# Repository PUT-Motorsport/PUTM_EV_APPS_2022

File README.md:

# Accelerator Pedal Position Sensor (APPS)

## Motivation

APPS handling is required by official FSG Rules according to T11.8 ([see](https://www.formulastudent.de/fileadmin/user_upload/all/2022/rules/FS-Rules_2022_v1.0.pdf#page=58)). APPS signals are system critical signals meaning that any implausibility between sensors or a failure should result in complete motor power shutdown.

## Pedal travel

* 0% - fully released
* 100% - fully applied

## Implausiblity

Implausibility is defined as a deviation of more than ten percentage points pedal travel
between any of the used APPSs. If it occurs for more than 100 ms the power to the motor must be immediately shut down.

## Platform

Software for APPS signal handling is developed using C++ for STM32 microcontroller.

## Program schematic

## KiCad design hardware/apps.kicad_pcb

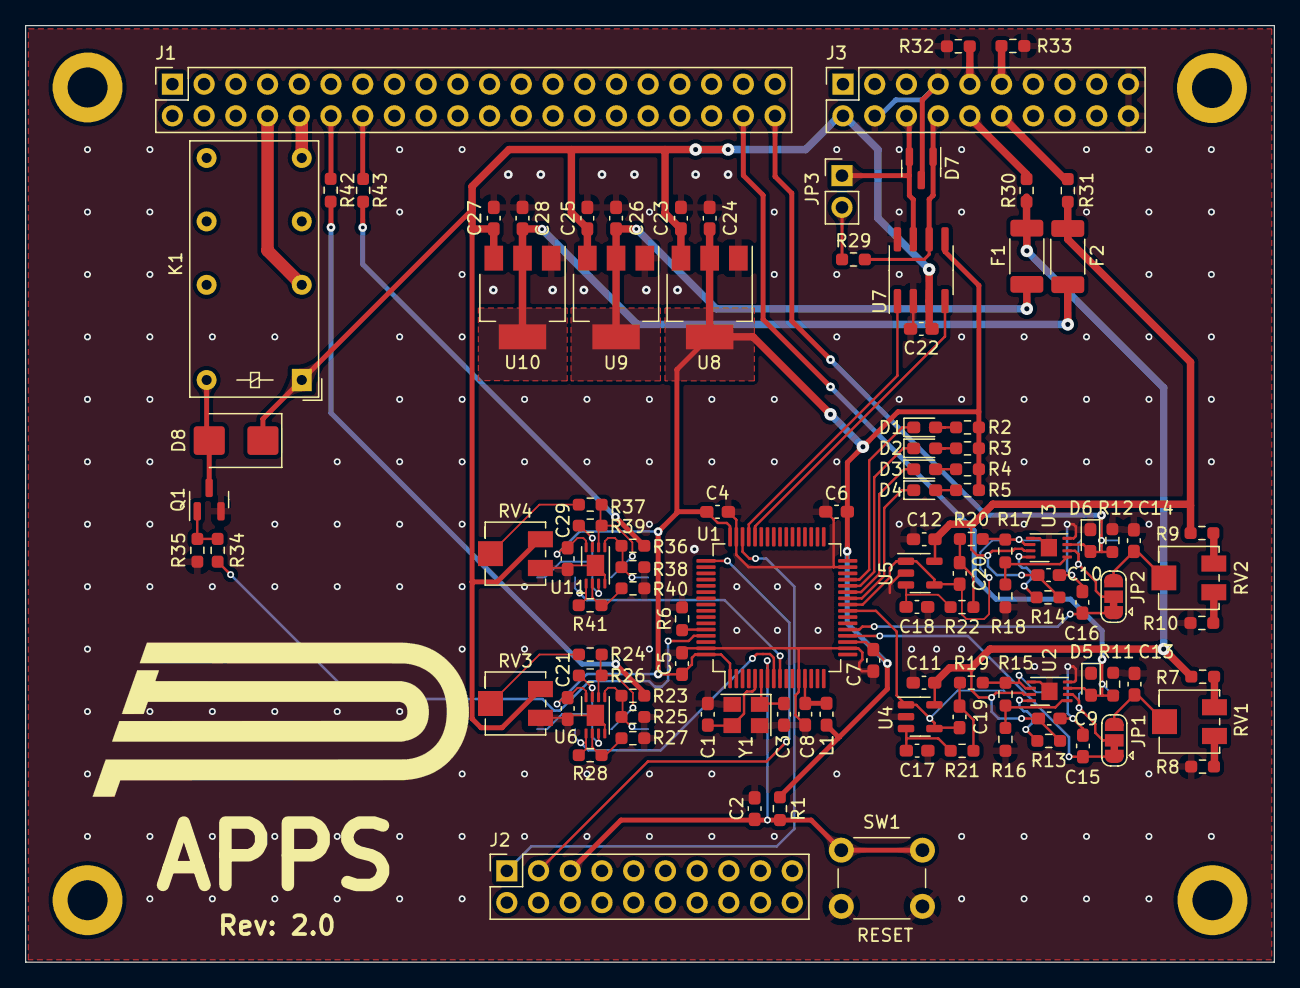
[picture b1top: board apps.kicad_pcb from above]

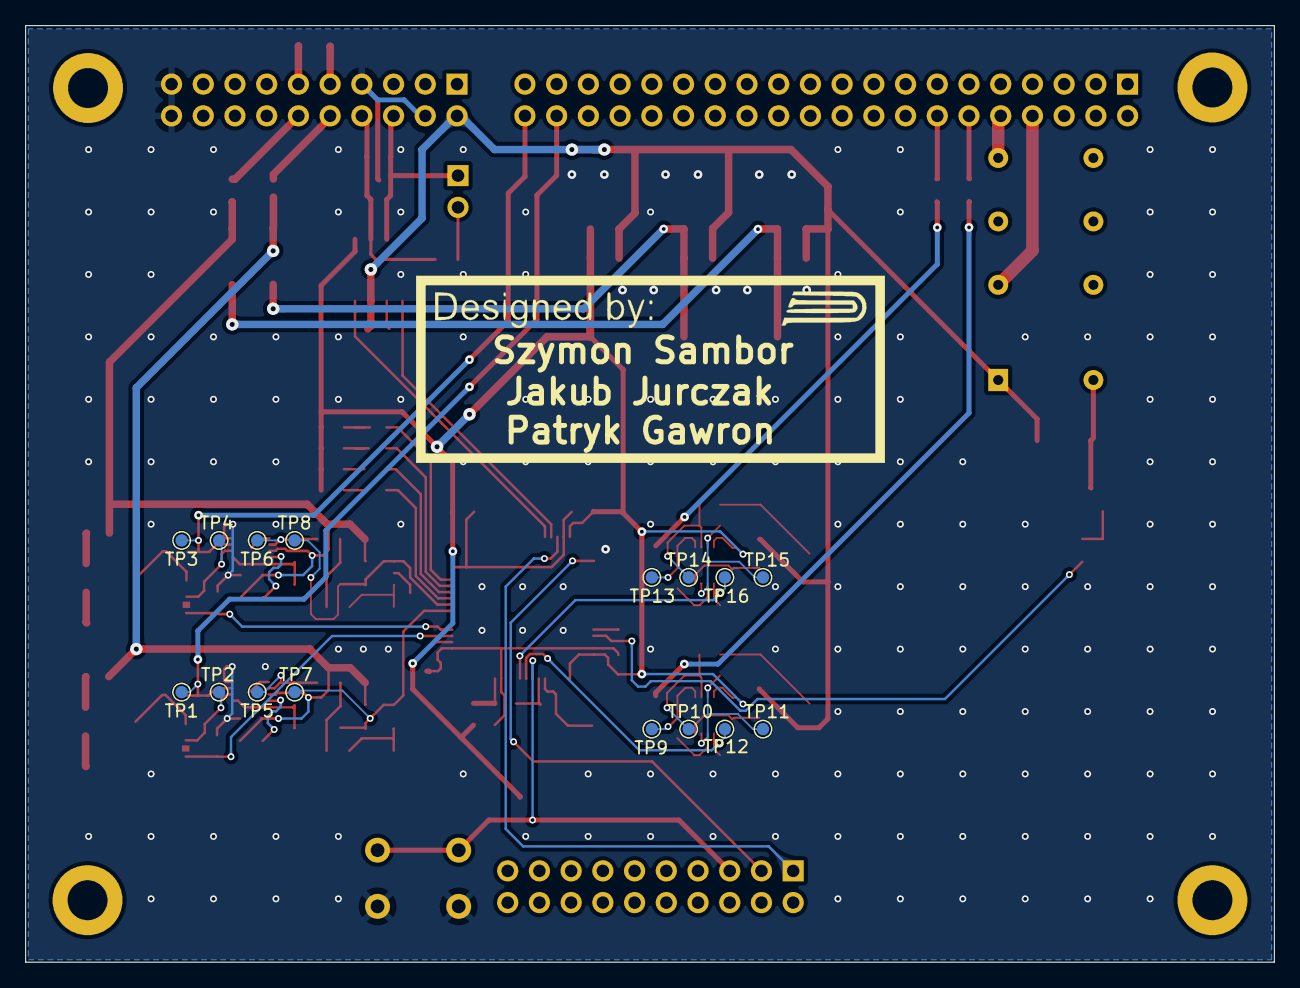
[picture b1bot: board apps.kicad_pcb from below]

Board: 2 copper layers, 100.0 x 75.0 mm, 124 parts (16 on the bottom side), 76 nets.

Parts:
C1, C3: 22p; C_0603_1608Metric_Pad1.08x0.95mm_HandSolder
C2, C4, C5, C6, C7, C8, C9, C10, C11, C12, C17, C18, C19, C20, C21, C22, C23, C24, C25, C26, C27, C28, C29: 100n; C_0603_1608Metric_Pad1.08x0.95mm_HandSolder
C13, C14, C15, C16: 10n; C_0603_1608Metric_Pad1.08x0.95mm_HandSolder
D1, D2, D3, D4: Yellow; LED_0603_1608Metric_Pad1.05x0.95mm_HandSolder
D5, D6: 24V; D_0603_1608Metric_Pad1.05x0.95mm_HandSolder
D7: PESD2CAN.215; SOT-23
D8: STPS340U; D_SMB
F1, F2: 500mA; Fuse_2010_5025Metric
J1: Signals; PinSocket_2x20_P2.54mm_Vertical
J2: Diagnostics; PinSocket_2x10_P2.54mm_Vertical
J3: Power & CAN; PinSocket_2x10_P2.54mm_Vertical
JP1, JP2: POT/DAC; SolderJumper-3_P1.3mm_Bridged12_RoundedPad1.0x1.5mm
JP3: Terminator; PinHeader_1x02_P2.54mm_Vertical
K1: FINDER-30.22; Relay_DPDT_Finder_30.22
L1: 10u; L_0603_1608Metric_Pad1.05x0.95mm_HandSolder
Q1: BSN20; SOT-23
R1, R6, R7, R9, R35: 10k; R_0603_1608Metric_Pad0.98x0.95mm_HandSolder
R2, R3, R4, R5: 300R; R_0603_1608Metric_Pad0.98x0.95mm_HandSolder
R8, R10: 33k; R_0603_1608Metric_Pad0.98x0.95mm_HandSolder
R11, R12: 100k; R_0603_1608Metric_Pad0.98x0.95mm_HandSolder
R13, R14, R23, R26, R28, R32, R36, R39, R41, R42, R43: 0R; R_0603_1608Metric_Pad0.98x0.95mm_HandSolder
R15, R19, R20, R21, R22: 4k7; R_0603_1608Metric_Pad0.98x0.95mm_HandSolder
R16, R18: 1k; R_0603_1608Metric_Pad0.98x0.95mm_HandSolder
R17: 6k2; R_0603_1608Metric_Pad0.98x0.95mm_HandSolder
R24, R25, R34, R37, R38: 100R; R_0603_1608Metric_Pad0.98x0.95mm_HandSolder
R27, R40: 3k3; R_0603_1608Metric_Pad0.98x0.95mm_HandSolder
R29: 120R; R_0603_1608Metric_Pad0.98x0.95mm_HandSolder
R30: 330R; R_0603_1608Metric_Pad0.98x0.95mm_HandSolder
R31, R33: 220R; R_0603_1608Metric_Pad0.98x0.95mm_HandSolder
RV1, RV2: 1k; Potentiometer_Bourns_3214J_Horizontal
RV3, RV4: 2k; Potentiometer_Bourns_3214J_Horizontal
SW1: Reset; SW_PUSH_6mm
TP1, TP3: APPS_P; TestPoint_Pad_D1.0mm
TP2, TP4: APPS_N; TestPoint_Pad_D1.0mm
TP5, TP6: APPS_MID; TestPoint_Pad_D1.0mm
TP7, TP8: APPS_OUT; TestPoint_Pad_D1.0mm
TP9, TP13: BR_P; TestPoint_Pad_D1.0mm
TP10, TP14: BR_N; TestPoint_Pad_D1.0mm
TP11, TP15: BR_MID; TestPoint_Pad_D1.0mm
TP12, TP16: BR_OUT; TestPoint_Pad_D1.0mm
U1: STM32L4P5RET6; LQFP-64_10x10mm_P0.5mm
U2, U3: MCP6N11-005; TDFN-8-1EP_3x2mm_P0.5mm_EP1.3x1.4mm
U4, U5: MCP6001; SOT-23-5
U6, U11: MCP6002-xMC; DFN-8-1EP_3x2mm_P0.5mm_EP1.7x1.4mm
U7: MCP2562-H-SN; SOIC-8_3.9x4.9mm_P1.27mm
U8, U9, U10: LM1117-3.3; SOT-223-3_TabPin2
Y1: 8MHz; Crystal_SMD_3225-4Pin_3.2x2.5mm

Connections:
3V3_POT1: C9.1, C11.1, F1.1, R7.1, R13.2, R30.1, U2.7 (V+), U4.5 (V+)
3V3_POT2: C10.1, C12.1, F2.1, R9.1, R14.2, R31.1, U3.7 (V+), U5.5 (V+)
+3V3: C4.1, C5.1, C6.1, C7.1, C21.1, C24.1, C29.1, L1.1, R1.2, R2.1, R3.2, R4.2, R5.1, U1.1 (VBAT), U1.19 (VDD), U1.32 (VDD), U1.48 (VDDUSB), U1.64 (VDD), U6.8 (V+), U7.5 (Vio), U8.2 (VO), U11.8 (V+)
+5V: C22.1, C23.1, C25.1, C27.1, D8.1 (K), J3.2, K1.A1, RV3.1, RV4.1, U7.3 (VDD), U8.3 (VI), U9.3 (VI), U10.3 (VI)
/APPS1: C19.2, TP7.1, U1.24 (PC4), U4.1, U4.4 (-)
/APPS2: C20.2, TP8.1, U1.25 (PC5), U5.1, U5.4 (-)
/BRK_PRESS1: R28.1, TP12.1, U1.8 (PC0), U6.1
/BRK_PRESS2: R41.1, TP16.1, U1.9 (PC1), U11.1
/CAN_RX: U1.44 (PA11), U7.4 (RXD)
/CAN_TX: U1.45 (PA12), U7.1 (TXD)
/DAC_REF1: C15.1, JP1.1 (A), U1.20 (PA4)
/DAC_REF2: C16.1, JP2.1 (A), U1.21 (PA5)
/EN_RELAY: R34.2, U1.61 (PB8)
/LED1: D1.1 (K), U1.29 (PB10)
/LED2: D2.1 (K), U1.28 (PB2)
/LED3: D3.1 (K), U1.27 (PB1)
/LED4: D4.1 (K), U1.26 (PB0)
/XTAL1: C1.1, U1.5 (PH0-OSC_IN), Y1.3
/XTAL2: C3.1, U1.6 (PH1-OSC_OUT), Y1.1
BRK_PRESS_LEFT: R23.2, R42.1
BRK_PRESS_RIGHT: R36.2, R43.1
CAN+: D7.2 (A2), J3.6, JP3.1, U7.7 (CANH)
CAN-: D7.1 (A1), J3.8, R29.2, U7.6 (CANL)
CLK: J2.3, U1.49 (PA14)
GND: C1.2, C2.2, C3.2, C4.2, C5.2, C6.2, C7.2, C8.2, C9.2, C10.2, C11.2, C12.2, C13.2, C14.2, C15.2, C16.2, C17.2, C18.2, C21.2, C22.2, C23.2, C24.2, C25.2, C26.2, C27.2, C28.2, C29.2, D5.1 (A1), D6.1 (A1), D7.3 (common), J3.4, J3.7, J3.19, J3.20, Q1.2 (S), R6.1, R8.2, R10.2, R11.2, R12.2, R16.1, R18.1, R25.1, R27.2, R32.1, R33.1, R35.2, R38.1, R40.2, RV3.3, RV4.3, SW1.1, U1.12 (VSSA/VREF-), U1.18 (VSS), U1.31 (VSS), U1.47 (VSS), U1.63 (VSS), U2.4 (V-), U2.5 (RF), U2.9 (EP), U3.4 (V-), U3.5 (RF), U3.9 (EP), U4.2 (V-), U5.2 (V-), U6.4 (V-), U6.9 (V-), U7.2 (VSS), U7.8 (STBY), U8.1 (GND), U9.1 (GND), U10.1 (GND), U11.4 (V-), U11.9 (V-), Y1.2, Y1.4
NRST: C2.1, J2.5, R1.1, SW1.2, U1.7 (NRST)
unnamed: C19.1, R19.2, R21.1
unnamed: C20.1, R20.2, R22.1
unnamed: D1.2 (A), R2.2
unnamed: D2.2 (A), R3.1
unnamed: D3.2 (A), R4.1
unnamed: D4.2 (A), R5.2
unnamed: D8.2 (A), K1.A2, Q1.3 (D)
unnamed: J1.12, R42.2
unnamed: J1.14, R43.2
unnamed: J3.9, R32.2
unnamed: J3.10, R30.2
unnamed: J3.11, R33.2
unnamed: J3.12, R31.2
unnamed: C13.1, JP1.3 (B), RV1.2
unnamed: JP1.2 (C), TP2.1, U2.2 (-)
unnamed: C14.1, JP2.3 (B), RV2.2
unnamed: JP2.2 (C), TP4.1, U3.2 (-)
unnamed: JP3.2, R29.1
unnamed: Q1.1 (G), R34.1, R35.1
unnamed: R7.2, RV1.1
unnamed: R8.1, RV1.3
unnamed: R9.2, RV2.1
unnamed: R10.1, RV2.3
unnamed: R15.2, R19.1, TP5.1, U2.6
unnamed: R17.2, R20.1, TP6.1, U3.6
unnamed: R24.2, RV3.2
unnamed: R37.2, RV4.2
unnamed: R6.2, U1.60 (PH3-BOOT)
unnamed: R13.1, U2.8 (EN)
unnamed: R15.1, R16.2, U2.1 (FG)
unnamed: R14.1, U3.8 (EN)
unnamed: R17.1, R18.2, U3.1 (FG)
unnamed: C17.1, R21.2, U4.3 (+)
unnamed: C18.1, R22.2, U5.3 (+)
unnamed: R26.1, TP11.1, U6.3 (+), U6.7
unnamed: R27.1, R28.2, U6.2 (-)
unnamed: R23.1, R25.2, TP9.1, U6.5 (+)
unnamed: R24.1, R26.2, TP10.1, U6.6 (-)
unnamed: C26.1, F1.2, U9.2 (VO)
unnamed: C28.1, F2.2, U10.2 (VO)
unnamed: R39.1, TP15.1, U11.3 (+), U11.7
unnamed: R40.1, R41.2, U11.2 (-)
unnamed: R36.1, R38.2, TP13.1, U11.5 (+)
unnamed: R37.1, R39.2, TP14.1, U11.6 (-)
SAFETY_IN: J1.8, K1.11
SAFETY_OUT: J1.10, K1.14
SIG_APPS1: D5.2 (A2), J1.38, R11.1, TP1.1, U2.3 (+)
SIG_APPS2: D6.2 (A2), J1.40, R12.1, TP3.1, U3.3 (+)
SWD: J2.1, U1.46 (PA13)
VDDA: C8.1, L1.2, U1.13 (VDDA/VREF+)

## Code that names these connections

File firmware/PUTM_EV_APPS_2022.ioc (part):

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Mcu.Name=STM32L4P5R(G-E)Tx
Mcu.Package=LQFP64
Mcu.UserName=STM32L4P5RETx
PA0.Mode=Asynchronous
PA0.Signal=UART4_TX
PA1.Mode=Asynchronous
PA1.Signal=UART4_RX
PA11.GPIOParameters=GPIO_Label
PA11.GPIO_Label=CAN_RX
PA11.Mode=CAN_Activate
PA11.Signal=CAN1_RX
PA12.GPIOParameters=GPIO_Label
PA12.GPIO_Label=CAN_TX
PA12.Mode=CAN_Activate
PA12.Signal=CAN1_TX
PA13\ (JTMS/SWDIO).Mode=Serial_Wire
PA13\ (JTMS/SWDIO).Signal=SYS_JTMS-SWDIO
PA14\ (JTCK/SWCLK).Mode=Serial_Wire
PA14\ (JTCK/SWCLK).Signal=SYS_JTCK-SWCLK
PA4.GPIOParameters=GPIO_Label
PA4.GPIO_Label=DAC_REF1
PA4.Signal=COMP_DAC11_group
PA5.GPIOParameters=GPIO_Label
PA5.GPIO_Label=DAC_REF2
PA5.Signal=COMP_DAC12_group
PB0.GPIOParameters=GPIO_Label
PB0.GPIO_Label=LED_4
PB0.Signal=GPIO_Output
PB1.GPIOParameters=GPIO_Label
PB1.GPIO_Label=LED_3
PB1.Signal=GPIO_Output
PB10.GPIOParameters=GPIO_Label
PB10.GPIO_Label=LED_1
PB10.Signal=GPIO_Output
PB2.GPIOParameters=GPIO_Label
PB2.GPIO_Label=LED_2
PB2.Signal=GPIO_Output
PB8.GPIOParameters=GPIO_Label
PB8.GPIO_Label=SAFETY
PB8.Signal=GPIO_Output
PC0.GPIOParameters=GPIO_Label
PC0.GPIO_Label=BRK_PRESS1
PC0.Signal=ADCx_IN1
PC1.GPIOParameters=GPIO_Label
PC1.GPIO_Label=BRK_PRESS2
PC1.Signal=ADCx_IN2
PC4.GPIOParameters=GPIO_Label
PC4.GPIO_Label=SENSOR_1
PC4.Signal=ADCx_IN13
PC5.GPIOParameters=GPIO_Label
PC5.GPIO_Label=SENSOR_2
PC5.Signal=ADCx_IN14
PH0-OSC_IN\ (PH0).Mode=HSE-External-Oscillator
PH0-OSC_IN\ (PH0).Signal=RCC_OSC_IN
PH1-OSC_OUT\ (PH1).Mode=HSE-External-Oscillator
PH1-OSC_OUT\ (PH1).Signal=RCC_OSC_OUT
RCC.HSE_VALUE=16000000
RCC.SYSCLKFreq_VALUE=32000000
RCC.SYSCLKSource=RCC_SYSCLKSOURCE_PLLCLK
board=custom

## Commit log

2022-04-27 .gitignore for Kicad and STM32 project
2022-04-27 STM32 project config + hardware files clean up
2022-04-27 README update
2022-04-27 Added CAN lib
2022-04-28 Added can_library as a example for sending and receiving data, CAN in LOOPBACK
2022-05-06 Calibration
2022-05-27 Tests on table config
2022-05-27 Working CAN interface and calibrated for pedal table stand.
2022-05-28 Corrected .gitignore to include Startup folder in Core
2022-05-29 Tested with TCS on cable harness + calibrated for car pedal.
2022-05-31 Calbirated APPS for table testing
2022-06-05 Calibration for PM-08
2022-06-22 New CAN lib + core refactor
2022-06-23 Code refactor
2022-07-24 Calibration 24.07.2022 new pedal mount.
2022-09-06 TS activation button + apps calibration
2023-04-11 Use in-amps for the analog inputs
2023-04-16 Kąkolewo quick fix
2023-04-21 Align components on the PCB
2023-04-21 KiCad project refactor
2023-04-22 Route PCB tracks
2023-04-22 Rename directories
2023-05-02 Add brake pressure sensors
2023-05-02 Add 0R resistors to the brake pressure signals
2023-05-02 Use bridged solder jumpers
2023-05-02 Change test points footprints
2023-05-05 Refactor
2023-05-31 Fix submodule path
2023-06-23 Update component values
2023-06-30 Adjust APPS values and implement brake pressure measurements
2023-06-30 Adjust component values
2023-07-08 Use voltage followers for the brake pressure measurements
2023-07-08 Send the real brake pressure values
2023-07-10 Send zeros on implausibility
2023-07-14 Don't send data from the second sensors for now
2023-08-20 Send data from the second brake pressure sensor
2023-09-04 FSP Hotfix: Shift the curves & send implausiblity state when needed
